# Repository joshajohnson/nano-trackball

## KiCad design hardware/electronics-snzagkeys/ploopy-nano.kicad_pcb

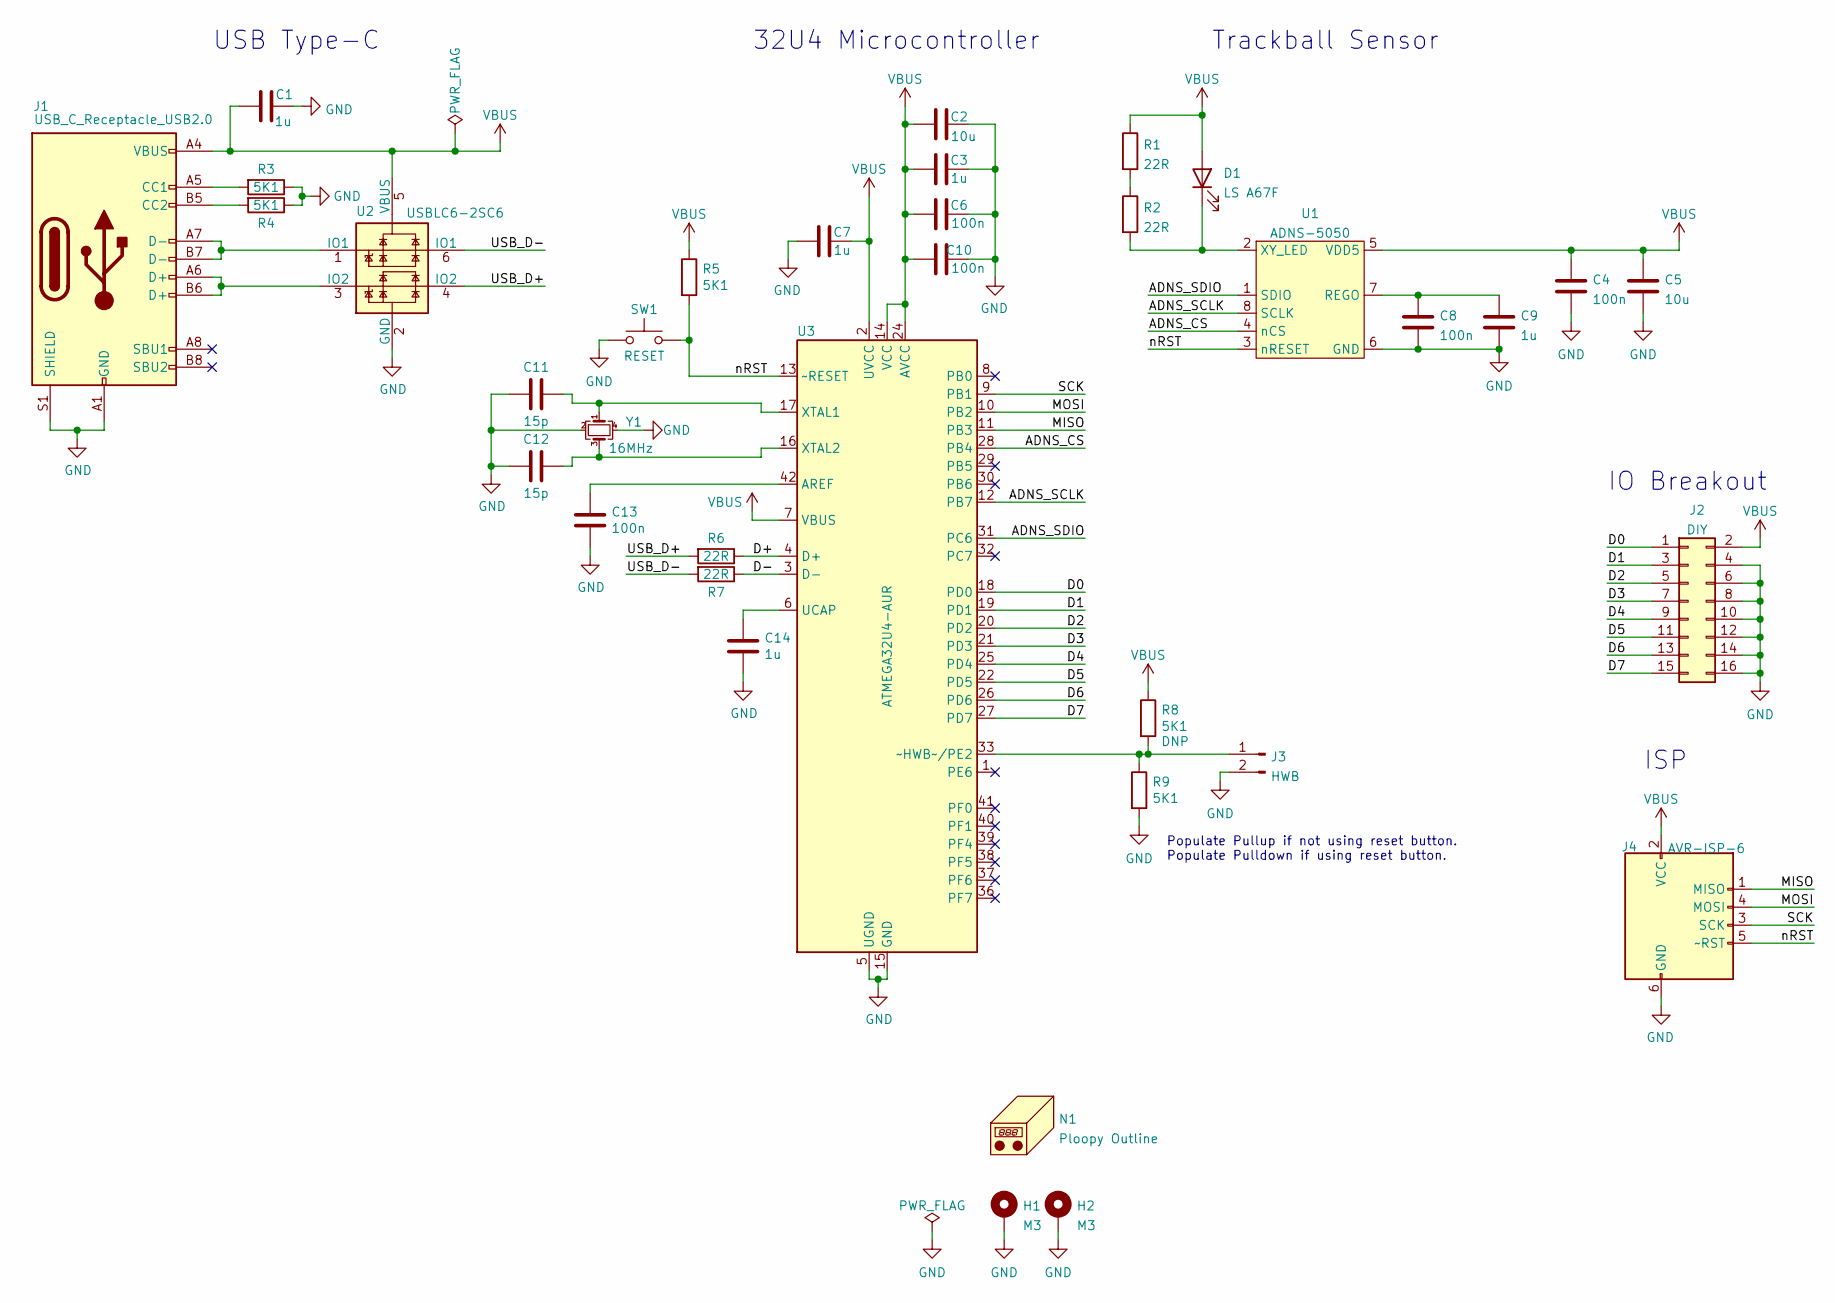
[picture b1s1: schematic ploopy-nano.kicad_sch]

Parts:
C1, C3, C7, C9, C14: 1u; C_0603_1608Metric; MPN CL10A105KO8NNNC; LCSC C1592
C2, C5: 10u; C_0603_1608Metric; MPN CL10A106MQ8NNNC; LCSC C1691
C4, C6, C8, C10, C13: 100n; C_0603_1608Metric; MPN CL10B104KO8NNNC; LCSC C66501
C11, C12: 15p; C_0603_1608Metric; MPN CL10C150JB8NNNC; LCSC C1644
D1: LS A67F; LO-A67F; MPN LS A67F-U2BA-1-3A4B-30-R33; LCSC C2830531
H1, H2: M3; MountingHole_3.2mm_M3_Pad_Via
J1: USB_C_Receptacle_USB2.0; USB_C_Receptacle_HRO_TYPE-C-31-M-12; MPN TYPE-C-31-M-14; LCSC C223907
J2: DIY; PinSocket_2x08_P2.54mm_Vertical
J3: HWB; PinHeader_1x02_P2.54mm_Vertical
J4: AVR-ISP-6; AVR_PROG_2.54_SMT
N1: Ploopy Outline; Ploopy-Nano
R1, R2, R6, R7: 22R; R_0603_1608Metric; MPN RC0603JR-0722RL; LCSC C108405
R3, R4, R5, R8, R9: 5K1; R_0603_1608Metric; MPN RC0603JR-075K1L; LCSC C14677
SW1: RESET; SW_Push_KMR2; MPN KMR221NGLFS; LCSC C269272
U1: ADNS-5050
U2: USBLC6-2SC6; SOT-23-6; MPN USBLC6-2SC6; LCSC C7519
U3: ATMEGA32U4-AUR; TQFP-44_10x10mm_P0.8mm; MPN ATMEGA32U4-AU; LCSC C44854
Y1: 16MHz; Crystal_SMD_3225-4Pin_3.2x2.5mm; MPN TAXM16M4RDBCCT2T; LCSC C164044

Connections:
/ADNS_CS: U1.4 (nCS), U3.28 (PB4)
/ADNS_SCLK: U1.8 (SCLK), U3.12 (PB7)
/ADNS_SDIO: U1.1 (SDIO), U3.31 (PC6)
/D0: J2.1, U3.18 (PD0)
/D1: J2.3, U3.19 (PD1)
/D2: J2.5, U3.20 (PD2)
/D3: J2.7, U3.21 (PD3)
/D4: J2.9, U3.25 (PD4)
/D5: J2.11, U3.22 (PD5)
/D6: J2.13, U3.26 (PD6)
/D7: J2.15, U3.27 (PD7)
/D+: R6.1, U3.4 (D+)
/D-: R7.1, U3.3 (D-)
/MISO: J4.1 (MISO), U3.11 (PB3)
/MOSI: J4.4 (MOSI), U3.10 (PB2)
/SCK: J4.3 (SCK), U3.9 (PB1)
/USB_D+: R6.2, U2.4 (IO2)
/USB_D-: R7.2, U2.6 (IO1)
/nRST: J4.5 (~RST), R5.2, SW1.2, U1.3 (nRESET), U3.13 (~RESET)
GND: C1.2, C2.2, C3.2, C4.2, C5.2, C6.2, C7.1, C8.2, C9.2, C10.2, C11.2, C12.2, C13.2, C14.2, H1.1, H2.1, J1.A1 (GND), J1.A12 (GND), J1.B1 (GND), J1.B12 (GND), J1.S1 (SHIELD), J2.4, J2.6, J2.8, J2.10, J2.12, J2.14, J2.16, J3.2, J4.6 (GND), R3.1, R4.1, R9.2, SW1.1, U1.6 (GND), U2.2 (GND), U3.5 (UGND), U3.15 (GND), U3.23 (GND), U3.35 (GND), U3.43 (GND), Y1.2, Y1.4
unnamed: C8.1, C9.1, U1.7 (REGO)
unnamed: C11.1, U3.17 (XTAL1), Y1.1
unnamed: C12.1, U3.16 (XTAL2), Y1.3
unnamed: C13.1, U3.42 (AREF)
unnamed: C14.1, U3.6 (UCAP)
unnamed: D1.1 (K), R2.2, U1.2 (XY_LED)
unnamed: J1.A5 (CC1), R3.2
unnamed: J1.A6 (D+), J1.B6 (D+), U2.3 (IO2)
unnamed: J1.A7 (D-), J1.B7 (D-), U2.1 (IO1)
unnamed: J1.B5 (CC2), R4.2
unnamed: J3.1, R8.2, R9.1, U3.33 (~HWB~/PE2)
unnamed: R1.2, R2.1
VBUS: C1.1, C2.1, C3.1, C4.1, C5.1, C6.1, C7.2, C10.1, D1.2 (A), J1.A4 (VBUS), J1.A9 (VBUS), J1.B4 (VBUS), J1.B9 (VBUS), J2.2, J4.2 (VCC), R1.1, R5.1, R8.1, U1.5 (VDD5), U2.5 (VBUS), U3.2 (UVCC), U3.7 (VBUS), U3.14 (VCC), U3.24 (AVCC), U3.34 (VCC), U3.44 (AVCC)

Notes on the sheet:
USB Type-C
32U4 Microcontroller
Populate Pullup if not using reset button. Populate Pulldown if using reset button.
Trackball Sensor
IO Breakout
ISP

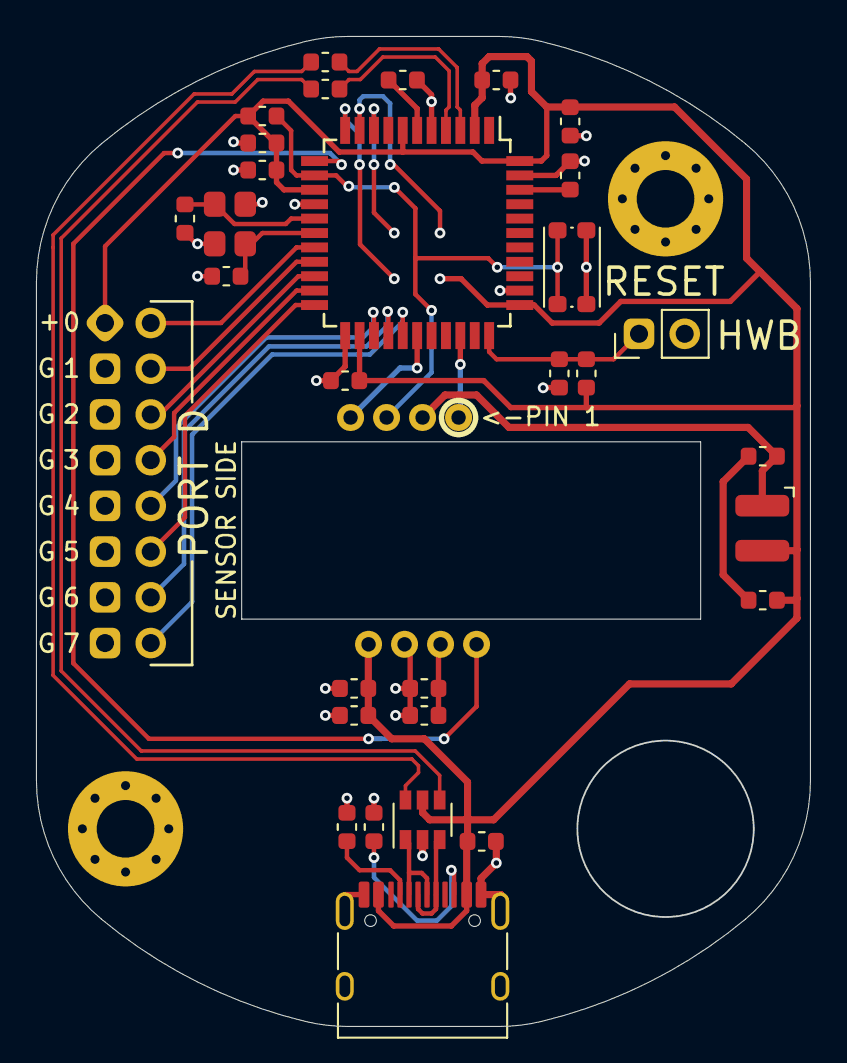
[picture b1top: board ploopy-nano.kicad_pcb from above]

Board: 2 copper layers, 43.0 x 55.0 mm, 36 parts (1 on the bottom side), 33 nets.

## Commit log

2021-08-11 add snzagkeys versionN

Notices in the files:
hardware/electronics-snzagkeys/ploopy-nano.kicad_pcb:
Licenced under CERN OHL v1.2
